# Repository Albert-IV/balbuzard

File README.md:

# Balbuzard

Balbuzard is a 36-key keyboard with a PCB. This repository contains the [Ergogen](https://github.com/mrzealot/ergogen) configuration that generates the KiCad PCB file.

## Usage

Assuming you have [npm installed](https://www.npmjs.com/get-npm):

``` sh
git clone --recursive git@github.com:brow/balbuzard.git
cd balbuzard
make
```

Find the generated PCB at `output/pcbs/main.kicad_pcb`.

## How do you type on that?

My keymap looks like this. The colors indicate which finger I use to hit each key.

## Rev 1.

* Ergogen config upgraded to latest 3.0.0
* Column layout tweaked, ready for routuing
* Each key / diode is routed.  Next is to route columns and rows (AKA the hard part)
* Removed routing done since I've found a way in Kicad to make direct connections (which will make the key routing cleaner looking)
* Redid the key / diode routing to use straight tracks wherever I could. 
* Just went ahead and used [an autorouter called Freerouter.](https://github.com/freerouting/freerouting/)
* After much gnashing of teeth, I have the scales SVG working.  Now to add to the front / back of PCB.

Front SVG Export:
Edge.Cuts
F.Silkscreen
F.Mask

Back SVG Export:
Edge.Cuts
B.Silkscreen
B.Mask

# TODO

* Add Balbuzard silkscreen on the front of the PCB
* Add something to the back of the PCB?  Thinking maybe a pattern like this: https://pattern.monster/scales-3/

**Note:** If there is a Rev 2. you will need to rotate the left side buttom-most thumb key's diode.  Rotated manually in Kicad to make it easier to route without routing on the back side.

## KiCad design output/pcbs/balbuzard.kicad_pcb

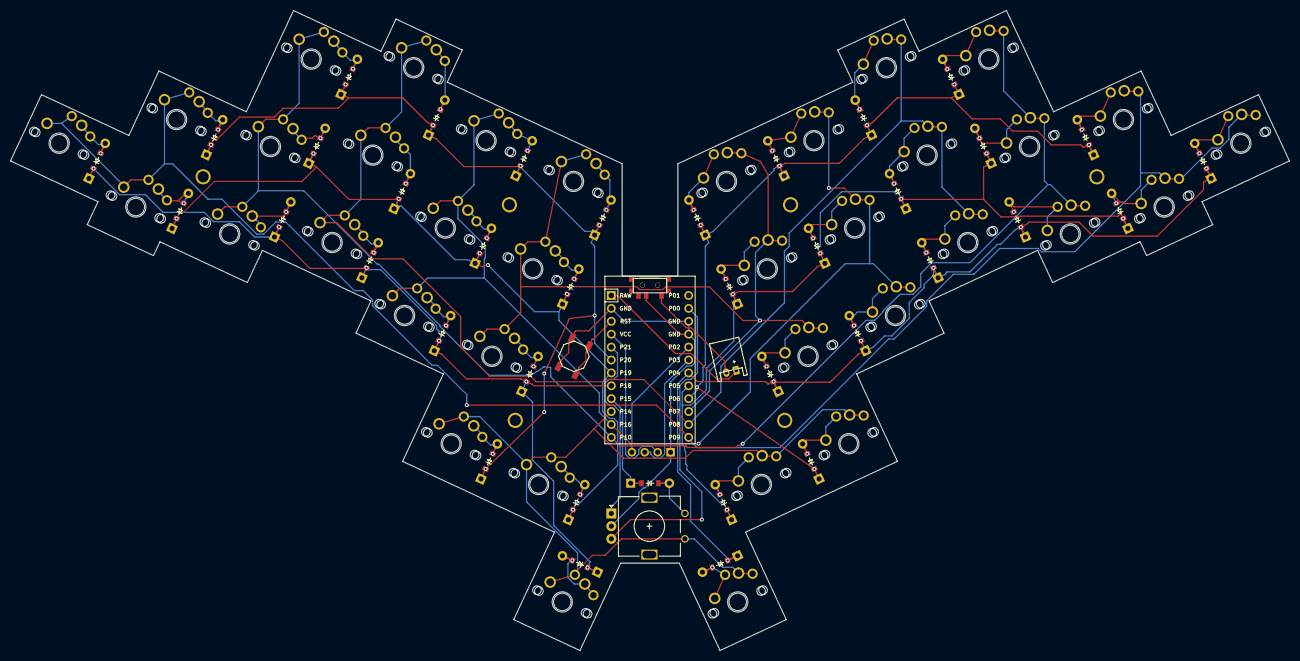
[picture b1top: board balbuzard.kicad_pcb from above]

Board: 2 copper layers, 251.9 x 126.1 mm, 121 parts (0 on the bottom side), 59 nets.

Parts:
B1: SW_TACT_ALPS_SKQGABE010
D1, D2, D3, D4, D5, D6, D7, D8, D9, D10, D11, D12, D13, D14, D15, D16, D17, D18, D19, D20, D21, D22, D23, D24, D25, D26, D27, D28, D29, D30, D31, D32, D33, D34, D35, D36, D37: ComboDiode
HOLE1, HOLE2, HOLE3, HOLE4, HOLE5, HOLE6: MountingHole_2.2mm_M2_Pad_Via
JST1: JST_PH_S2B-PH-K_02x2.00mm_Angled
MCU1: ProMicro
OLED1: OLED; OLED_headers
ROT1: rotary_encoder
S1, S3, S5, S7, S9, S11, S13, S15, S17, S19, S21, S23, S25, S27, S29, S31, S33, S35, S37, S39, S41, S43, S45, S47, S49, S51, S53, S55, S57, S59, S61, S63, S65, S67, S69, S71: MX
S2, S4, S6, S8, S10, S12, S14, S16, S18, S20, S22, S24, S26, S28, S30, S32, S34, S36, S38, S40, S42, S44, S46, S48, S50, S52, S54, S56, S58, S60, S62, S64, S66, S68, S70, S72: PG1350
T1: SPDT_C128955

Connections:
GND: B1.2, MCU1.2, MCU1.15, MCU1.16, OLED1.1, ROT1.C, T1.2
P0: MCU1.14, ROT1.B
P2: MCU1.17, OLED1.4
P3: MCU1.18, OLED1.3
P4: D19.1, D19.2, D22.1, D22.2, D25.1, D25.2, D28.1, D28.2, D31.1, D31.2, D36.1, D36.2, MCU1.19
P5: D20.1, D20.2, D23.1, D23.2, D26.1, D26.2, D29.1, D29.2, D32.1, D32.2, D35.1, D35.2, MCU1.20
P6: D21.1, D21.2, D24.1, D24.2, D27.1, D27.2, D30.1, D30.2, D33.1, D33.2, D34.1, D34.2, MCU1.21
P7: MCU1.22, S25.2, S26.2, S27.2, S28.2, S29.2, S30.2, S61.1, S62.1, S63.1, S64.1, S65.1, S66.1
P8: MCU1.23, S13.2, S14.2, S15.2, S16.2, S17.2, S18.2, S49.1, S50.1, S51.1, S52.1, S53.1, S54.1
P9: MCU1.24, S1.2, S2.2, S3.2, S4.2, S5.2, S6.2, S37.1, S38.1, S39.1, S40.1, S41.1, S42.1
P10: MCU1.12, S7.2, S8.2, S9.2, S10.2, S11.2, S12.2, S43.1, S44.1, S45.1, S46.1, S47.1, S48.1
P14: MCU1.10, ROT1.2, S31.2, S32.2, S33.2, S34.2, S35.2, S36.2, S67.1, S68.1, S69.1, S70.1, S71.1, S72.1
P15: D37.1, D37.2, MCU1.9
P16: MCU1.11, S19.2, S20.2, S21.2, S22.2, S23.2, S24.2, S55.1, S56.1, S57.1, S58.1, S59.1, S60.1
P18: D1.1, D1.2, D4.1, D4.2, D7.1, D7.2, D10.1, D10.2, D13.1, D13.2, D18.1, D18.2, MCU1.8
P19: D2.1, D2.2, D5.1, D5.2, D8.1, D8.2, D11.1, D11.2, D14.1, D14.2, D17.1, D17.2, MCU1.7
P20: D3.1, D3.2, D6.1, D6.2, D9.1, D9.2, D12.1, D12.2, D15.1, D15.2, D16.1, D16.2, MCU1.6
P21: MCU1.5, ROT1.A
RAW: JST1.1, MCU1.1
RST: B1.1, MCU1.3
VCC: MCU1.4, OLED1.2
far_thumb: D18.1, D18.2, S35.1, S36.1
home_thumb: D17.1, D17.2, S33.1, S34.1
index_bottom: D10.1, D10.2, S19.1, S20.1
index_home: D11.1, D11.2, S21.1, S22.1
index_top: D12.1, D12.2, S23.1, S24.1
inner_bottom: D13.1, D13.2, S25.1, S26.1
inner_home: D14.1, D14.2, S27.1, S28.1
inner_top: D15.1, D15.2, S29.1, S30.1
middle_bottom: D7.1, D7.2, S13.1, S14.1
middle_home: D8.1, D8.2, S15.1, S16.1
middle_top: D9.1, D9.2, S17.1, S18.1
mirror_far_thumb: D36.1, D36.2, S71.2, S72.2
mirror_home_thumb: D35.1, D35.2, S69.2, S70.2
mirror_index_bottom: D28.1, D28.2, S55.2, S56.2
mirror_index_home: D29.1, D29.2, S57.2, S58.2
mirror_index_top: D30.1, D30.2, S59.2, S60.2
mirror_inner_bottom: D31.1, D31.2, S61.2, S62.2
mirror_inner_home: D32.1, D32.2, S63.2, S64.2
mirror_inner_top: D33.1, D33.2, S65.2, S66.2
mirror_middle_bottom: D25.1, D25.2, S49.2, S50.2
mirror_middle_home: D26.1, D26.2, S51.2, S52.2
mirror_middle_top: D27.1, D27.2, S53.2, S54.2
mirror_near_thumb: D34.1, D34.2, S67.2, S68.2
mirror_pinky_bottom: D19.1, D19.2, S37.2, S38.2
mirror_pinky_home: D20.1, D20.2, S39.2, S40.2
mirror_pinky_top: D21.1, D21.2, S41.2, S42.2
mirror_ring_bottom: D22.1, D22.2, S43.2, S44.2
mirror_ring_home: D23.1, D23.2, S45.2, S46.2
mirror_ring_top: D24.1, D24.2, S47.2, S48.2
near_thumb: D16.1, D16.2, S31.1, S32.1
pinky_bottom: D1.1, D1.2, S1.1, S2.1
pinky_home: D2.1, D2.2, S3.1, S4.1
pinky_top: D3.1, D3.2, S5.1, S6.1
ring_bottom: D4.1, D4.2, S7.1, S8.1
ring_home: D5.1, D5.2, S9.1, S10.1
ring_top: D6.1, D6.2, S11.1, S12.1
rotary_diode: D37.1, D37.2, ROT1.1
slider_positive: JST1.2, T1.1

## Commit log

2021-11-11 Began work on routing and updating dependencies. Right now both make and npm can compile, will probably remove the Makefile eventually. Had a couple of nice tweaks I might submit a PR for
2021-11-11 Removed submodule shenanigans
2021-11-12 Went from OG config.yml -> balbuzard.yml and fixed compilation, then deleted Alps because they're Alps and one one uses them.
2021-11-12 Also commit this too
2021-11-22 Fixed the nets, broke the project. Hoo boy!
2021-11-22 Fixed the broken layout by adding the rows again
2021-11-22 Don't include the a-tux config, only included to compare notes
2021-11-23 Routing fixed, added encoder and on / off switch. Last that is left is JST connector and reset button
2021-11-23 Added reset button
2021-11-23 Flipped the JST connector to be correct
2021-11-30 Mounting holes: Added
2021-11-30 Create rev1 directory, time to begin routing!
2021-11-30 Fix issue with thumb mirror not reversing switch pins
2021-12-01 Routed individual keys, added info on progress
2021-12-01 Removed routing, found a better way
2021-12-01 Redid the key / diode tracks to be as straight as possible.
2021-12-01 Maybe fix github readme
2021-12-01 Fixed README directly in Github
2021-12-02 Went ahead and used an autorouter to do traces. Did 90% of the work for me (hopefully)
2021-12-05 Added waves SVG for silkscreens and added a copper fill.
2022-01-25 Finished Rev1 PCB and sent off to be manufactured. Repo is in need of a huge cleanup effort
2022-01-25 Finished Rev1 PCB and sent off to be manufactured. Repo is in need of a huge cleanup effort
    Add photo of PCB
    Removed svg2shenzen cache items
    Removed svg2shenzen cache items
    Added svg2shenzen cache to git ignore
2022-01-25 Update README.md
    Update image?
2022-01-25 Rename jpg
2022-01-25 Update README.md
    Fix image again
2022-01-25 Update README.md
    Ugh, capitalization am I right?
